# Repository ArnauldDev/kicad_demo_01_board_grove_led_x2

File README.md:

# Réseau des Electroniciens

<https://www.electroniciens.cnrs.fr/>

- [Bienvenue sur les pages wiki du groupe CAO](https://wiki.electroniciens.cnrs.fr/index.php/Le_groupe_CAO) > [KiCad](https://wiki.electroniciens.cnrs.fr/index.php/CAO_:_KICAD)

# Demo 01 : LED Control Mode - Grove Interface

Réaliser une carte électronique compatible avec les connectiques GROVE, exemple d'une Shield au format UNO :

## Exemple de cartes identiques

- [Grove - LED Socket Kit](http://wiki.seeedstudio.com/Grove-LED_Socket_Kit/)
- [Grove - Red LED](http://wiki.seeedstudio.com/Grove-Red_LED/)

mais pas de modules avec deux LED : <http://wiki.seeedstudio.com/Display/>

Donc à partir des conventions des modules Grove, nous allons réaliser notre propre carte
voir "[les différentes tailles standardisées des modules Grove](http://wiki.seeedstudio.com/Grove_System/#size-of-grove)"

Comment dans KiCad importer un DXF pour réaliser le contour layer du PCB
voir "[6.1.2. Utilisation d’un dessin DXF pour le contour du circuit](http://docs.kicad-pcb.org/stable/fr/pcbnew.html#_creation_d_8217_un_circuit)"

Réalisation du contour d'une carte au format DXF sur le modèle d'un module Grove 1x2 avec un logiciel de CAO FreeCAD/Inventor/SolidWorks

- Taille du module : [20x40 mm](img/freecad-esquisse-pcb-20x40mm.png)
- Source "[Grove Mechnical Drawing](https://github.com/SeeedDocument/GroveSystem/tree/master/res)" : [Grove-20x40mm.pdf](https://github.com/SeeedDocument/GroveSystem/blob/master/res/Grove-40x40-SMD-horizontal/Grove-%E8%B4%B4%E7%89%87%E5%BA%A7%E5%AD%90-%E8%BA%BA.pdf)

[Épaisseur de circuit imprimé & Matière](https://www.wedirekt.fr/fr/web/technologie/pcb-technologie/sp-cification/dimensions-et-mati-re.fs-1235901.html)

---

## Application KiCad (64-bit)

Version: (6.0.5), release build

```txt
  Libraries:
    wxWidgets 3.1.5
    libcurl/7.82.0-DEV Schannel zlib/1.2.12

  Platform: Windows 10 (build 22000), 64-bit edition, 64 bit, Little endian, wxMSW

  Build Info:
    Date: May  3 2022 00:36:16
    wxWidgets: 3.1.5 (wchar_t,wx containers)
    Boost: 1.79.0
    OCC: 7.6.0
    Curl: 7.82.0-DEV
    ngspice: 36
    Compiler: Visual C++ 1929 without C++ ABI

  Build settings:
    KICAD_USE_OCC=ON
    KICAD_SPICE=ON
```

## Nouveau projet

Créer un nouveau projet "demo_carte_led" dans "C:\cao\kicad\projects", pas besoin de créer un répertoire pour le projet, un dossier sera créer automatiquement.

### Ajouter des composants

- Device:LED
  - 2x value LED
- Device:R
  - 2x value 220
- Connector_Generic:Conn_01x04
  - 1x value GROVE

# Les empreintes des composants d'usage courant

- footprint LED_THT:LED_D5.0mm
- footprint Resistor_THT:R_Axial_DIN0207_L6.3mm_D2.5mm_P10.16mm_Horizontal
- footprint Connector_JST:JST_PH_B4B-PH-K_1x04_P2.00mm_Vertical

[7. Association Composants - Empreintes avec CvPcb](http://docs.kicad-pcb.org/stable/fr/cvpcb.html#_association_composants_empreintes_avec_cvpcb)

# Fichier d'association des symboles aux empreintes

L'extension du nom des fichiers d'association est en *.equ

voir ["Association Automatique"](https://docs.kicad.org/6.0/fr/cvpcb/cvpcb.html#association_automatique_ou_manuelle)

Exemple : ..\demo_carte_led\association_fp.equ

---

## Application FreeCAD

<https://www.freecadweb.org/?lang=fr>

```txt
OS: Windows 10 Version 2009
Word size of OS: 64-bit
Word size of FreeCAD: 64-bit
Version: 0.19.24267 +148 (Git)
Build type: Release
Branch: Branch_0.19.4
Hash: 476ecf091941bead59b14e44afa6064d5a66afa3
Python version: 3.8.6+
Qt version: 5.15.2
Coin version: 4.0.1
OCC version: 7.5.3
Locale: French/France (fr_FR)
```

Depuis le menu **Fichier > Exporter**; sélectionner le **Sketch** de **Body** pour obtenir un contour de carte correcte, puis choisir le format **Autodesk DXF 2D (*.dxf)** :

Et voici le test de l'import dans KiCad :

### FreeCAD Documentation

Wiki : [Aide en ligne - table des matières](https://wiki.freecadweb.org/Online_Help_Toc/fr)

* [Atelier PCB](https://wiki.freecadweb.org/PCB_Workbench/fr)
* [Atelier KicadStepUp](https://wiki.freecadweb.org/KicadStepUp_Workbench/fr)

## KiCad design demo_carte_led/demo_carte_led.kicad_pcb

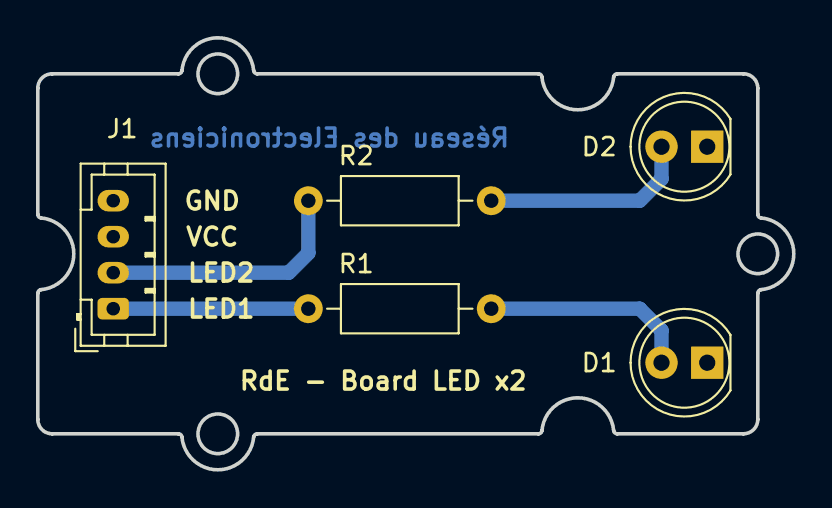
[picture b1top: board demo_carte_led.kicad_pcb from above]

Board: 2 copper layers, 42.0 x 24.0 mm, 5 parts (0 on the bottom side), 5 nets.

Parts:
D1, D2: LED; LED_D5.0mm
J1: GROVE; JST_PH_B4B-PH-K_1x04_P2.00mm_Vertical
R1, R2: 220; R_Axial_DIN0207_L6.3mm_D2.5mm_P10.16mm_Horizontal

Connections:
unnamed: D1.1 (K), D2.1 (K), J1.4
unnamed: D1.2 (A), R1.1
unnamed: D2.2 (A), R2.1
unnamed: J1.1, R1.2
unnamed: J1.2, R2.2

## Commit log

2018-11-30 Demonstration of making an electronic card with the open source software KiCad
2022-05-29 Mise à jour vers KiCAD 6 + Fichier FreeCAD
2022-05-29 MAJ de l'export sous FreeCAD
